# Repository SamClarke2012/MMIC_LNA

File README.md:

MMIC_LNA
========

Using ERA-3SM

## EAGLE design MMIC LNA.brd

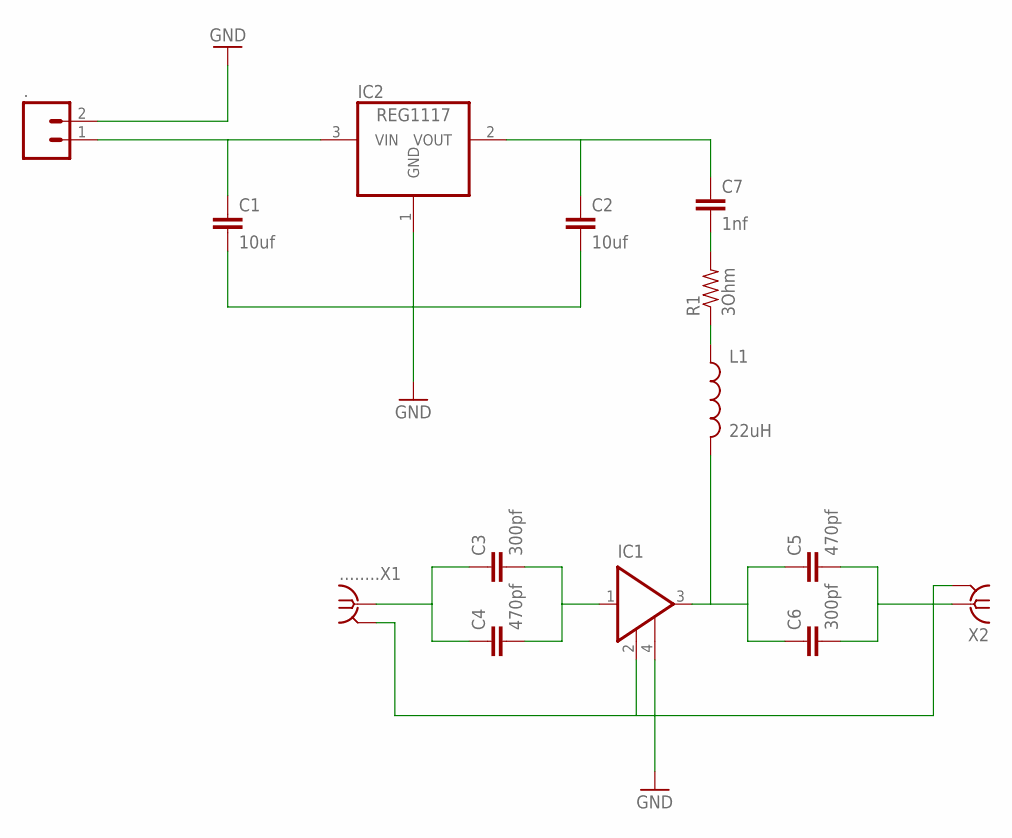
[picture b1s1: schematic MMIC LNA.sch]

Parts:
.: M02LOCK_LONGPADS; 1X02_LOCK_LONGPADS
........X1: BU-SMA-V
C1, C2: 10uf; 0603-CAP
C3, C6: 300pf; 0603-CAP
C4, C5: 470pf; 0603-CAP
C7: 1nf; 0603-CAP
IC1: ERA-3SM; WW
IC2: REG1117; SOT223
L1: 22uH; 0603
R1: 3Ohm; 0603-RES
X2: BU-SMA-V

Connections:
GND: ..2, ........X1.2, ........X1.3 (2), ........X1.4 (2), ........X1.5 (2), C1.2, C2.2, IC1.2 (GND), IC1.4 (GND), IC2.1 (GND), X2.2, X2.3 (2), X2.4 (2), X2.5 (2)
unnamed: ..1, C1.1, IC2.3 (VIN)
unnamed: C5.1, C6.1, IC1.3 (RFOUT/DCIN), L1.2
unnamed: C2.1, C7.1, IC2.2 (VOUT)
unnamed: C7.2, R1.2
unnamed: L1.1, R1.1
unnamed: C5.2, C6.2, X2.1
unnamed: C3.2, C4.2, IC1.1 (RFIN)
unnamed: ........X1.1, C3.1, C4.1

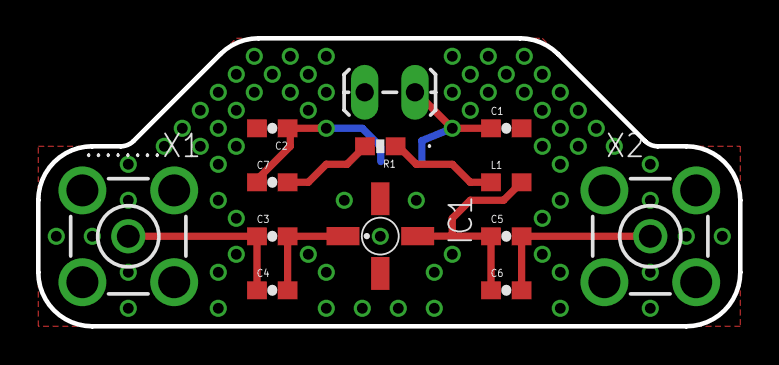
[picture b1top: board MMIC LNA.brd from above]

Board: 2 copper layers, 39.0 x 16.0 mm, 14 parts (1 on the bottom side), 9 nets.

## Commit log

2014-10-11 init

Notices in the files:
parts and their libraries:
SparkFun-Capacitors: Licensing: Creative Commons ShareAlike 4.0 International - https://creativecommons.org/licenses/by-sa/4.0
